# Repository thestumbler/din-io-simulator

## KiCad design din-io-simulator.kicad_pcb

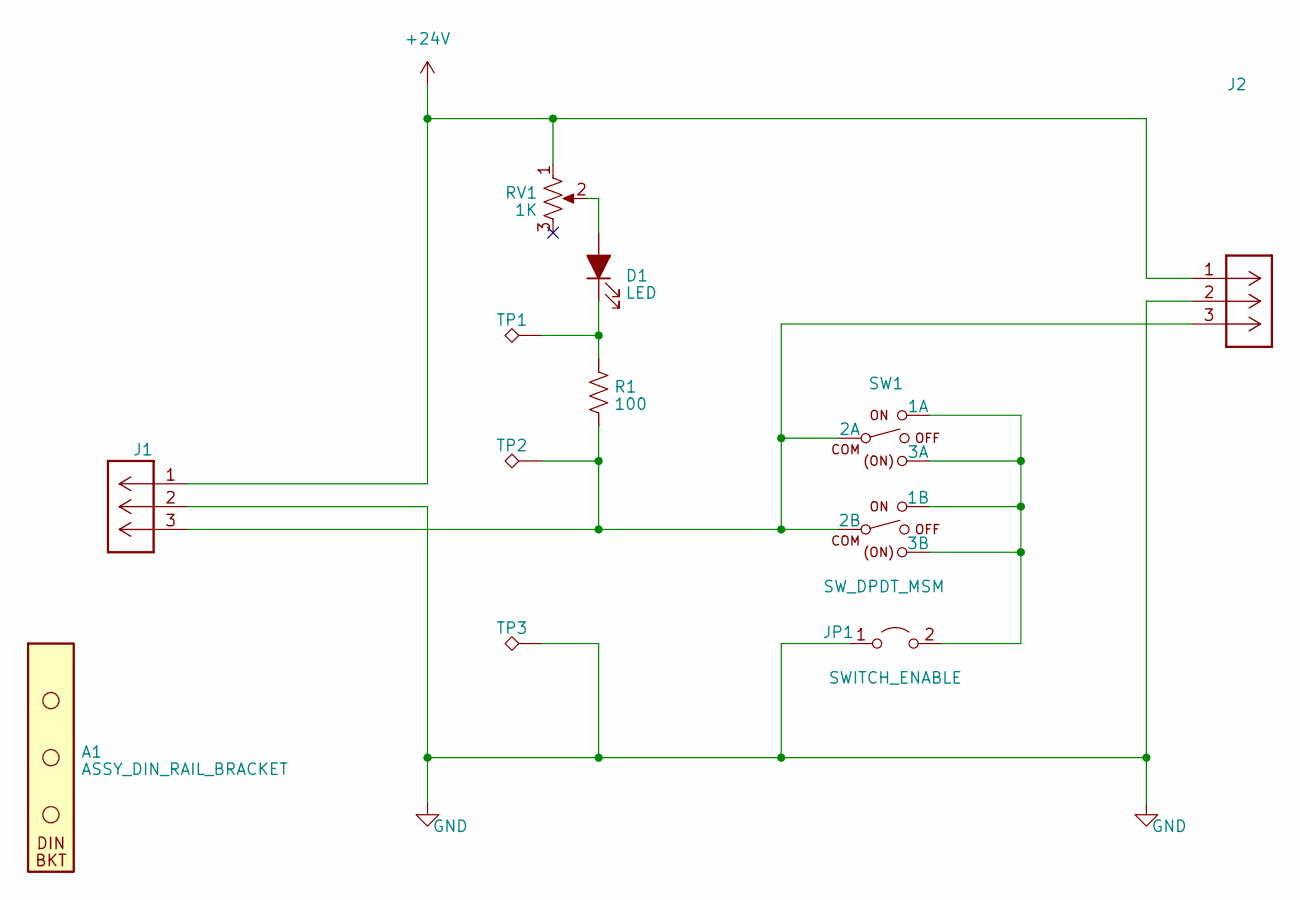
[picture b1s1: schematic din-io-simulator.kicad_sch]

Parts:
A1: ASSY_DIN_RAIL_BRACKET; BRACKET_DIN_RAIL_2HOLES
D1: LED; LED_D5.0mm
J1: IO1; TE_640454-3
J2: IO2; TE_640454-3
JP1: SWITCH_ENABLE; PinHeader_1x02_P2.54mm_Vertical
R1: 100; R_0805_2012Metric
RV1: 1K; Potentiometer_Bourns_3296W_Vertical
SW1: SW_DPDT_MSM; SW_100AWDP1T2B4M2QE
TP1, TP2, TP3: TestPoint; TestPoint_Keystone_5000-5004_Miniature

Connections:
+24V: J1.1, J2.1, RV1.1
GND: J1.2, J2.2, JP1.1 (A), TP3.1
unnamed: D1.2 (A), RV1.2
unnamed: D1.1 (K), R1.1, TP1.1
unnamed: J1.3, J2.3, R1.2, SW1.2 (2A), SW1.5 (2B), TP2.1
unnamed: JP1.2 (B), SW1.1 (1A), SW1.3 (3A), SW1.4 (1B), SW1.6 (3B)

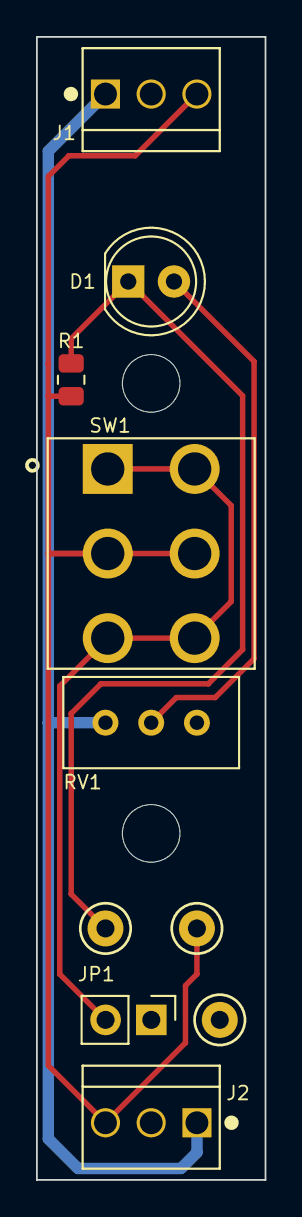
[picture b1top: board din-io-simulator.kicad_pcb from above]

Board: 2 copper layers, 12.7 x 63.5 mm, 11 parts (1 on the bottom side), 6 nets.

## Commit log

2023-03-06 initial release
2023-06-15 added scad files to repo
